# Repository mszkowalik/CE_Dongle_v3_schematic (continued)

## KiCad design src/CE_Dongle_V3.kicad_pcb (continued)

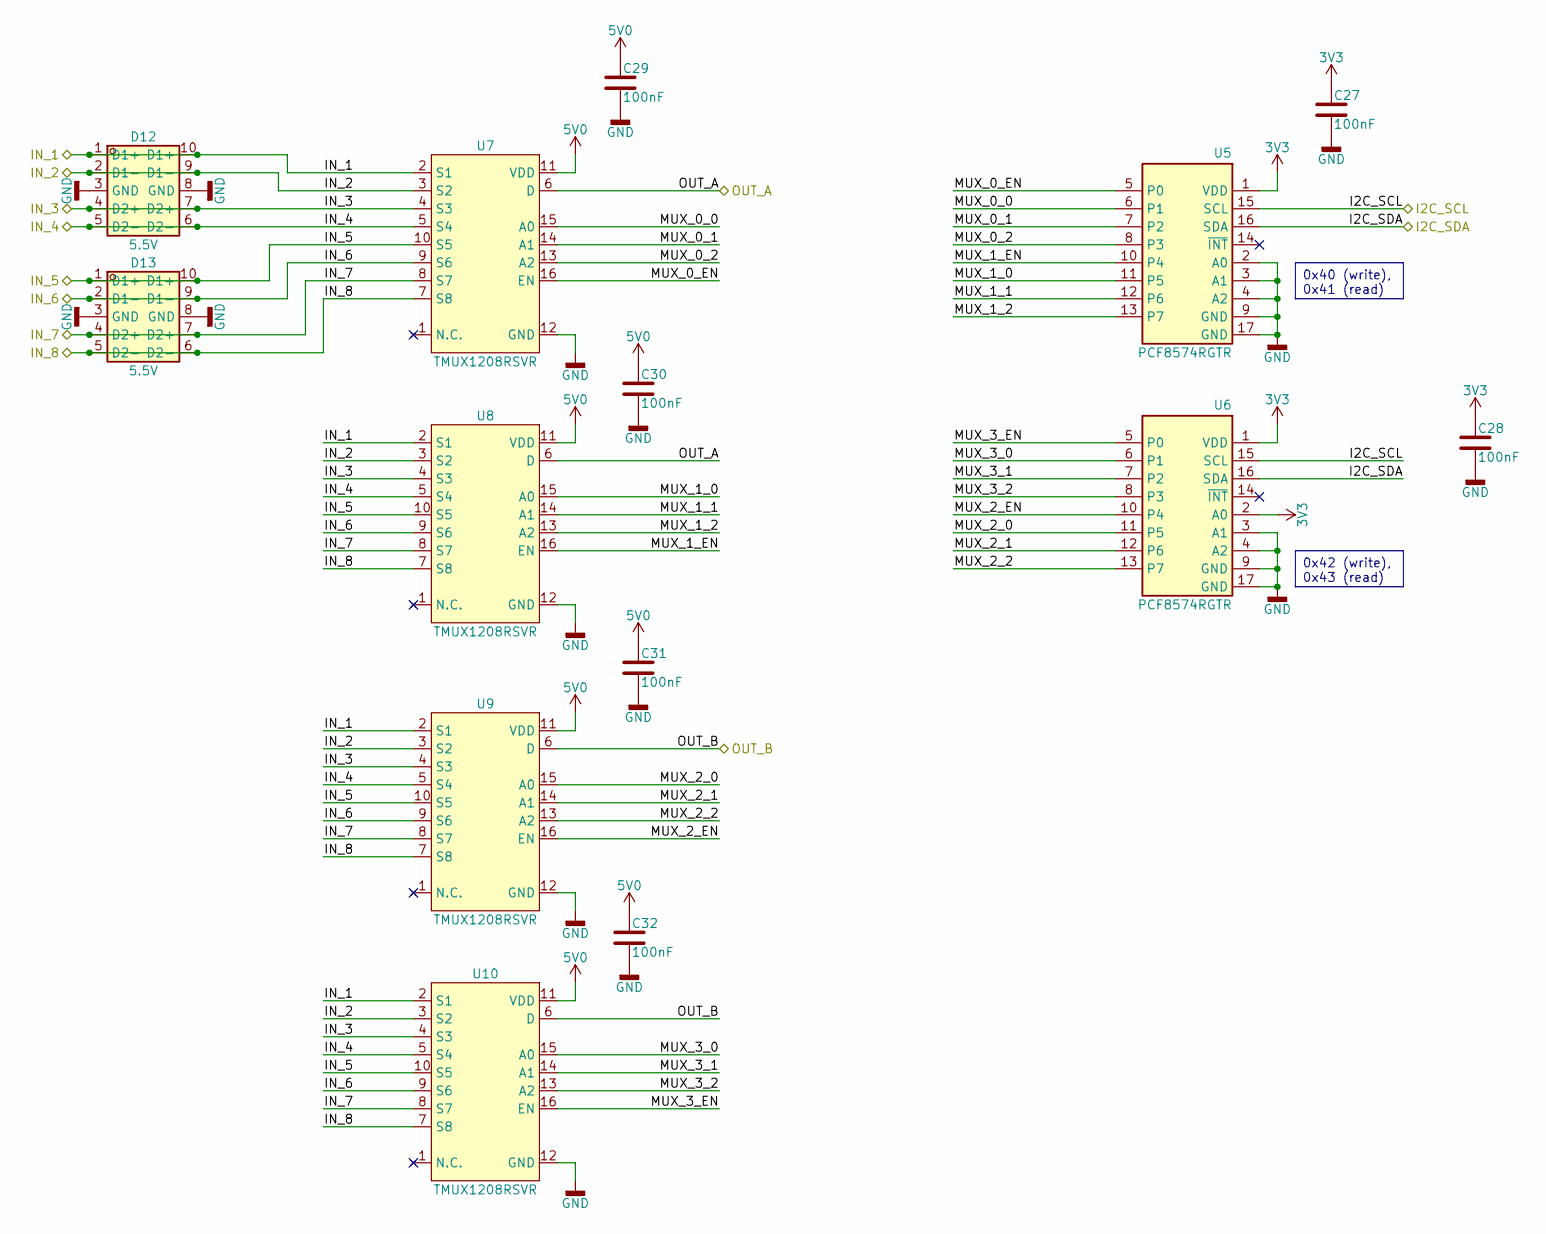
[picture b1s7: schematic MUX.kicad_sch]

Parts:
C27, C28, C29, C30, C31, C32: 100nF; C_0402_1005Metric; Voltage 16V; Tolerance 10%; Manufacturer Part Numbe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 CL05B104KO5NNNC; LCSC Part C1525
D12, D13: 5.5V; USON-10_2.5x1.0mm_P0.5mm; Voltage - Breakdown 6.5V; LCSC Part C138714
U5, U6: PCF8574RGTR; QFN-16-1EP_3x3mm_P0.5mm_EP1.7x1.7mm_ThermalVias; Manufacturer Part Numbe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 PCF8574RGTR; LCSC Part C22396384
U7, U8, U9, U10: TMUX1208RSVR; UQFN-16_1.8x2.6mm_P0.4mm; Manufacturer Part Numbe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 TMUX1208RSVR; LCSC Part C2673274

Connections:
3V3: C27.1, C28.1, U5.1 (VDD), U6.1 (VDD), U6.2 (A0); also elsewhere on the board
5V0: C29.1, C30.1, C31.1, C32.1, U7.11 (VDD), U8.11 (VDD), U9.11 (VDD), U10.11 (VDD); also elsewhere on the board
/MCU/I2C_SCL: U5.15 (SCL), U6.15 (SCL); also elsewhere on the board
/MCU/I2C_SDA: U5.16 (SDA), U6.16 (SDA); also elsewhere on the board
/MUX/IN_1: D12.1 (D1+), D12.10 (D1+), U7.2 (S1), U8.2 (S1), U9.2 (S1), U10.2 (S1); also elsewhere on the board
/MUX/IN_2: D12.2 (D1-), D12.9 (D1-), U7.3 (S2), U8.3 (S2), U9.3 (S2), U10.3 (S2); also elsewhere on the board
/MUX/IN_3: D12.4 (D2+), D12.7 (D2+), U7.4 (S3), U8.4 (S3), U9.4 (S3), U10.4 (S3); also elsewhere on the board
/MUX/IN_4: D12.5 (D2-), D12.6 (D2-), U7.5 (S4), U8.5 (S4), U9.5 (S4), U10.5 (S4); also elsewhere on the board
/MUX/IN_5: D13.1 (D1+), D13.10 (D1+), U7.10 (S5), U8.10 (S5), U9.10 (S5), U10.10 (S5); also elsewhere on the board
/MUX/IN_6: D13.2 (D1-), D13.9 (D1-), U7.9 (S6), U8.9 (S6), U9.9 (S6), U10.9 (S6); also elsewhere on the board
/MUX/IN_7: D13.4 (D2+), D13.7 (D2+), U7.8 (S7), U8.8 (S7), U9.8 (S7), U10.8 (S7); also elsewhere on the board
/MUX/IN_8: D13.5 (D2-), D13.6 (D2-), U7.7 (S8), U8.7 (S8), U9.7 (S8), U10.7 (S8); also elsewhere on the board
/MUX/MUX_0_0: U5.6 (P1), U7.15 (A0)
/MUX/MUX_0_1: U5.7 (P2), U7.14 (A1)
/MUX/MUX_0_2: U5.8 (P3), U7.13 (A2)
/MUX/MUX_0_EN: U5.5 (P0), U7.16 (EN)
/MUX/MUX_1_0: U5.11 (P5), U8.15 (A0)
/MUX/MUX_1_1: U5.12 (P6), U8.14 (A1)
/MUX/MUX_1_2: U5.13 (P7), U8.13 (A2)
/MUX/MUX_1_EN: U5.10 (P4), U8.16 (EN)
/MUX/MUX_2_0: U6.11 (P5), U9.15 (A0)
/MUX/MUX_2_1: U6.12 (P6), U9.14 (A1)
/MUX/MUX_2_2: U6.13 (P7), U9.13 (A2)
/MUX/MUX_2_EN: U6.10 (P4), U9.16 (EN)
/MUX/MUX_3_0: U6.6 (P1), U10.15 (A0)
/MUX/MUX_3_1: U6.7 (P2), U10.14 (A1)
/MUX/MUX_3_2: U6.8 (P3), U10.13 (A2)
/MUX/MUX_3_EN: U6.5 (P0), U10.16 (EN)
/MUX/OUT_A: U7.6 (D), U8.6 (D); also elsewhere on the board
/MUX/OUT_B: U9.6 (D), U10.6 (D); also elsewhere on the board
GND: C27.2, C28.2, C29.2, C30.2, C31.2, C32.2, D12.3 (GND), D12.8 (GND), D13.3 (GND), D13.8 (GND), U5.2 (A0), U5.3 (A1), U5.4 (A2), U5.9 (GND), U5.17 (GND), U6.3 (A1), U6.4 (A2), U6.9 (GND), U6.17 (GND), U7.12 (GND), U8.12 (GND), U9.12 (GND), U10.12 (GND); also elsewhere on the board

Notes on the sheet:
0x40 (write), 0x41 (read)
0x42 (write), 0x43 (read)

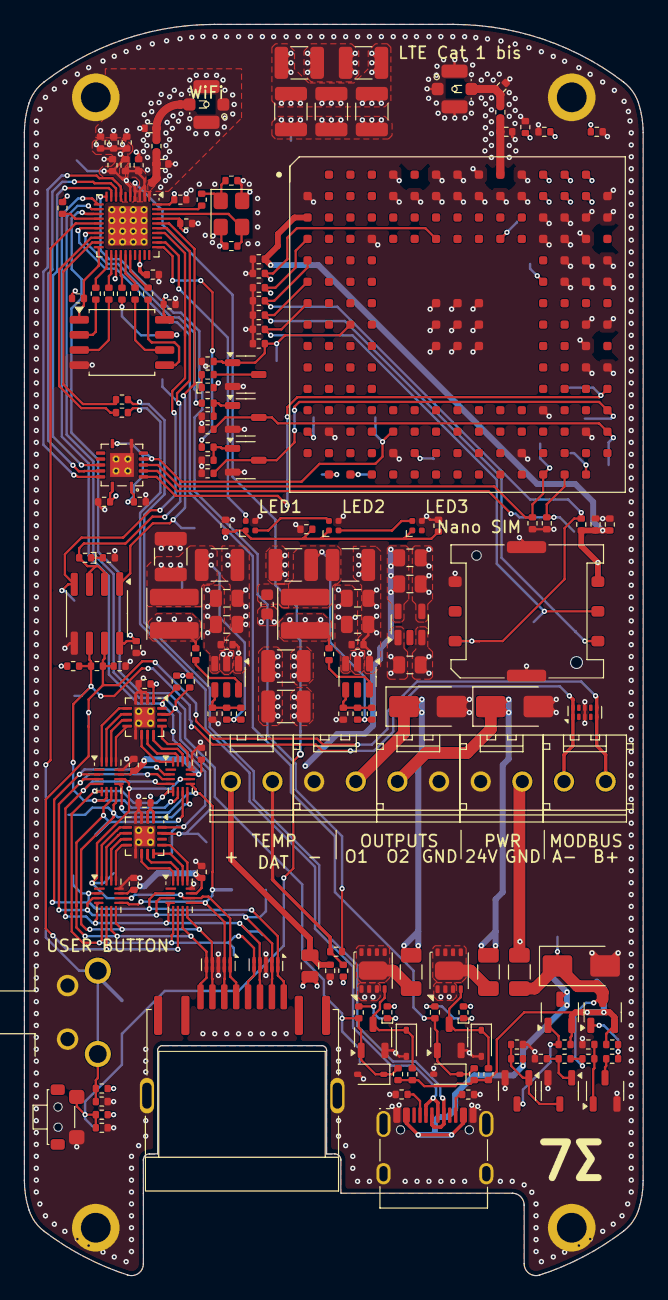
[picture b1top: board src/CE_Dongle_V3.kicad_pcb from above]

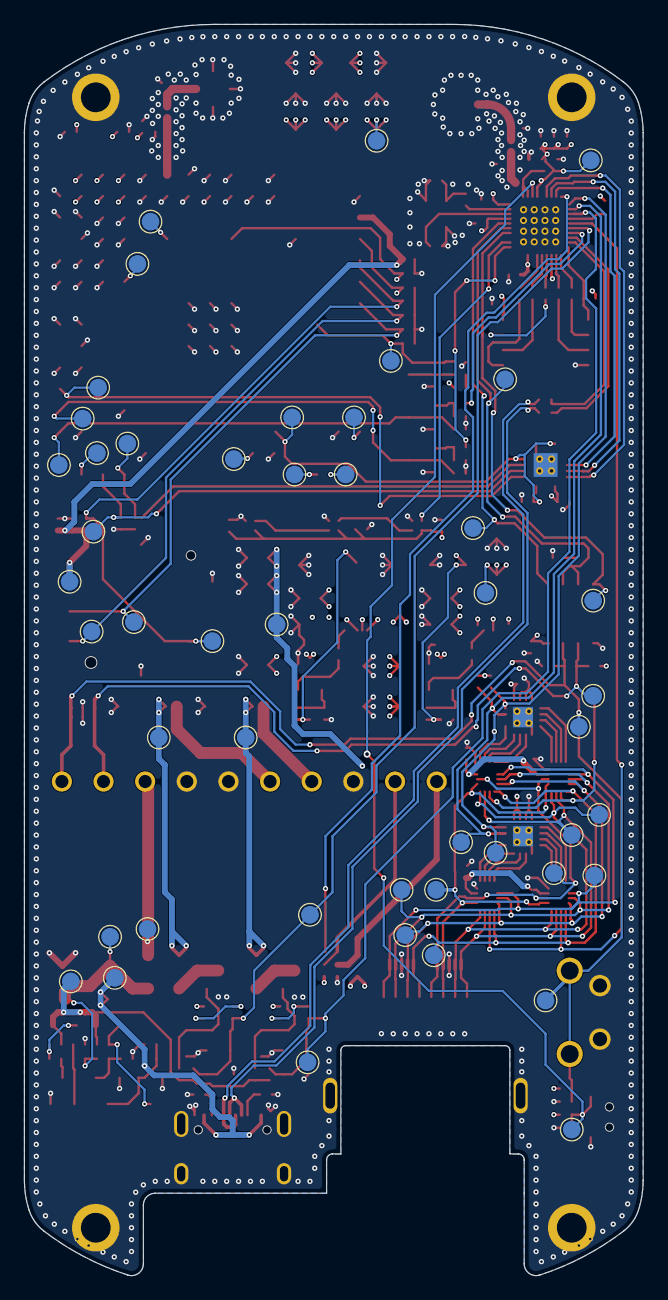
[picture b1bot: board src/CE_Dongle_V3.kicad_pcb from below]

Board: 4 copper layers, 52.0 x 105.2 mm, 240 parts (47 on the bottom side), 127 nets.

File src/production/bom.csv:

Designator,Footprint,Quantity,Value,LCSC Part #
"C1, C24, C4, C64",0402,4,1uF,C1518208
"C10, C11, C19, C22, C25, C26, C27, C28, C29, C30, C31, C32, C40, C46, C47, C48, C49, C50, C51, C54, C6, C66, C7, C8, C81, C9, C90, C91, C92",0402,29,100nF,C1525
"C12, C13",0402,2,10uF,C315248
"C14, C15",0402,2,1.2pF,C76899
"C16, C17",0402,2,12pF,C106201
"C18, C20, C33, C34, C35, C36, C37, C38, C39, C82",0402,10,100pF,C1546
"C2, C21, C23, C80, C84, C85, C86, C87",0805,8,10uF,C440198
"C3, C42, C43, C44, C45, C5, C55, C56, C57, C78, C79, C83, C93",1210,13,47uF,C2932477
C41,0402,1,220pF,C107001
"C52, C53",0402,2,10nF,C15195
"C62, C63, C65, C67, C68, C69",0402,6,33pF,C107005
"D1, D10",D_SMA,2,SMAJ28CA,C148228
"D11, D6, D9",D_SMA,3,SS34,C727060
D12,D_SOD-123,1,5V1,C173407
"D2, D3, D5, D8",0402,4,LTST-C281KRKT,C364556
ENC1,HAMMOND_1551XFLGY,1,Hammond_1551XFLGY,
FB1,0603,1,68nH,C76893
J1,USB-3.1-SMD_U262-161N-4BVC11,1,USB_C_Receptacle_USB2.0_16P,C319148
"J10, J2, J3, J6, J8",CONN-TH_DB301V-3.5-2P-GN,5,Conn_01x02,C695629
"J4, J5",SMA-SMD_BWSMA-KE-P001,2,Conn_Coaxial,C496550
J7,RJ45-TH_RC01812,1,8P8C_LED_Shielded,C708645
J9,SIM-SMD_NANO-SIM-TL6P-H1.35,1,SIM_NANO_Socket,C7529385
"K1, K2",RELAY-SMD_G6K-2F-X-XX,2,G6K-2F-Y-TR DC5,C47190
"L1, L2",0402,2,2.2nH,C91240
"L4, L5, L6",L_Changjiang_FTC404030S,3,4.7uH,C39676083
"LP1, LP2, LP3",FIX-LEMB2-4.8V0-F,3,FIX-LEMB2-4.8V0-F,
"Q1, Q2",SOT-23-3,2,AO3401A,C15127
"Q11, Q12, Q13, Q14, Q15, Q16, Q17, Q18",SOT-23-3,8,SI2308A,C347491
"Q7, Q8",SOT-23-3,2,BC817-40-7-F,C435867
"R10, R11, R12, R13, R15, R16, R17",0402,7,22R,C25092
"R18, R44",0402,2,120R,C25079
"R2, R30, R48, R55, R56, R59, R6, R71",0402,8,22K,C25768
"R20, R29, R3, R4, R5, R57, R60",0402,7,1K,C11702
"R21, R22, R31, R35, R36, R45, R51, R52, R61, R69",0402,10,10K,C25744
"R25, R26, R27, R28, R33, R34, R39, R47, R62, R70, R72",0402,11,100K,C25741
"R37, R38, R40",0402,3,374K,C25781
"R42, R43, R49, R8, R9",0402,5,5K1,C25905
R46,0402,1,0R,C17168
R50,0805,1,120R,C17437
R58,0402,1,162K,C54068
R7,0402,1,118K,C25748
SW1,SW-SMD_TS24CA,1,TS24CA,C393942
SW2,SW-SMD_4P-L6.0-W6.0-P4.50-LS9.0-H7.0,1,KH-6X6X7H-STM,C2837533
"TP1, TP10, TP11, TP12, TP13, TP14, TP15, TP16, TP17, TP18, TP19, TP2, TP20, TP21, TP22, TP23, TP24, TP7, TP8, TP9",TestPoint_Pad_D1.5mm,20,TestPoint,
U1,VQFN-40-1EP_5x5mm_P0.4mm_EP3.3x3.3mm_ThermalVias,1,ESP32-C6,C5364646
"U10, U7, U8, U9",UQFN-16_1.8x2.6mm_P0.4mm,4,TMUX1208RSVR,C2673274
"U14, U19, U4",SOT-23-6,3,TPS54302DDCR,C311983
U15,VQFN-14_L3.5-W3.5-P0.50-BL-EP-ThermalVias,1,TXS0104ERGYR,C154926
U16,XCVR_LE910R1-EU,1,LE910R1,
"U17, U18, U20",LED-SMD_4P-L1.3-W1.3-P0.80_WS2812E-1313,3,WS2812,C5446700
U2,SOIC-8_3.9x4.9mm_P1.27mm,1,SP3485,C8963
U3,SOIC-8_5.3x5.3mm_P1.27mm,1,W25Q64JVSSIQ,C179171
"U5, U6",QFN-16-1EP_3x3mm_P0.5mm_EP1.7x1.7mm_ThermalVias,2,PCF8574RGTR(UMW),C22396384
Y1,Crystal_SMD_3225-4Pin_3.2x2.5mm,1,40MHz,C37635390

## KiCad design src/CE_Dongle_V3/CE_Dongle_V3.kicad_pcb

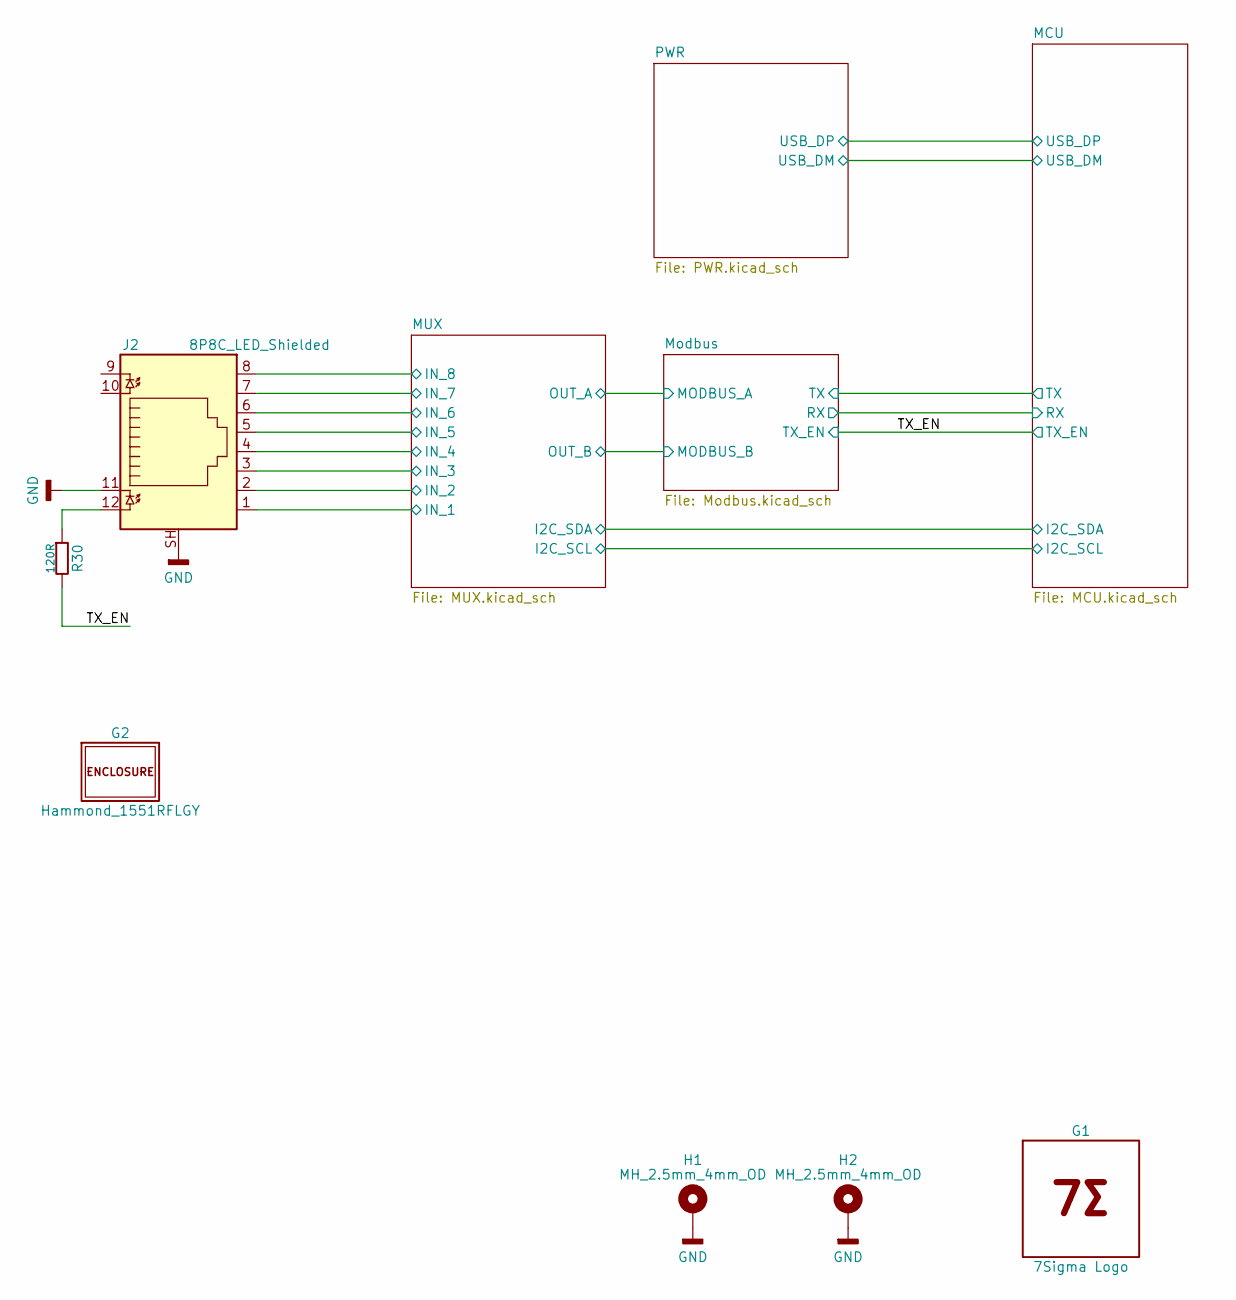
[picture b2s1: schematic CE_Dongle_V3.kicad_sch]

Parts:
G1: 7Sigma Logo; 7Sigma_Logo
G2: Hammond_1551RFLGY; HAMMOND_1551RFLGY
H1, H2: MH_2.5mm_4mm_OD; MountingHole_2.5mm_Pad_4mm
J2: 8P8C_LED_Shielded; RJ45-TH_RC01812; Manufacturer Part Numbe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 RC01812; LCSC Part C708645
R30: 120R; R_0402_1005Metric; Tolerance 1%; Manufacturer Part Numbe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 0402WGF1200TCE; LCSC Part C25079

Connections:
/MUX/MUX_IN_1: J2.1; also elsewhere on the board
/MUX/MUX_IN_2: J2.2; also elsewhere on the board
/MUX/MUX_IN_3: J2.3; also elsewhere on the board
/MUX/MUX_IN_4: J2.4; also elsewhere on the board
/MUX/MUX_IN_5: J2.5; also elsewhere on the board
/MUX/MUX_IN_6: J2.6; also elsewhere on the board
/MUX/MUX_IN_7: J2.7; also elsewhere on the board
/MUX/MUX_IN_8: J2.8; also elsewhere on the board
/TX_EN: R30.2; also elsewhere on the board
GND: H1.1, H2.1, J2.11, J2.SH; also elsewhere on the board
unnamed: J2.12, R30.1

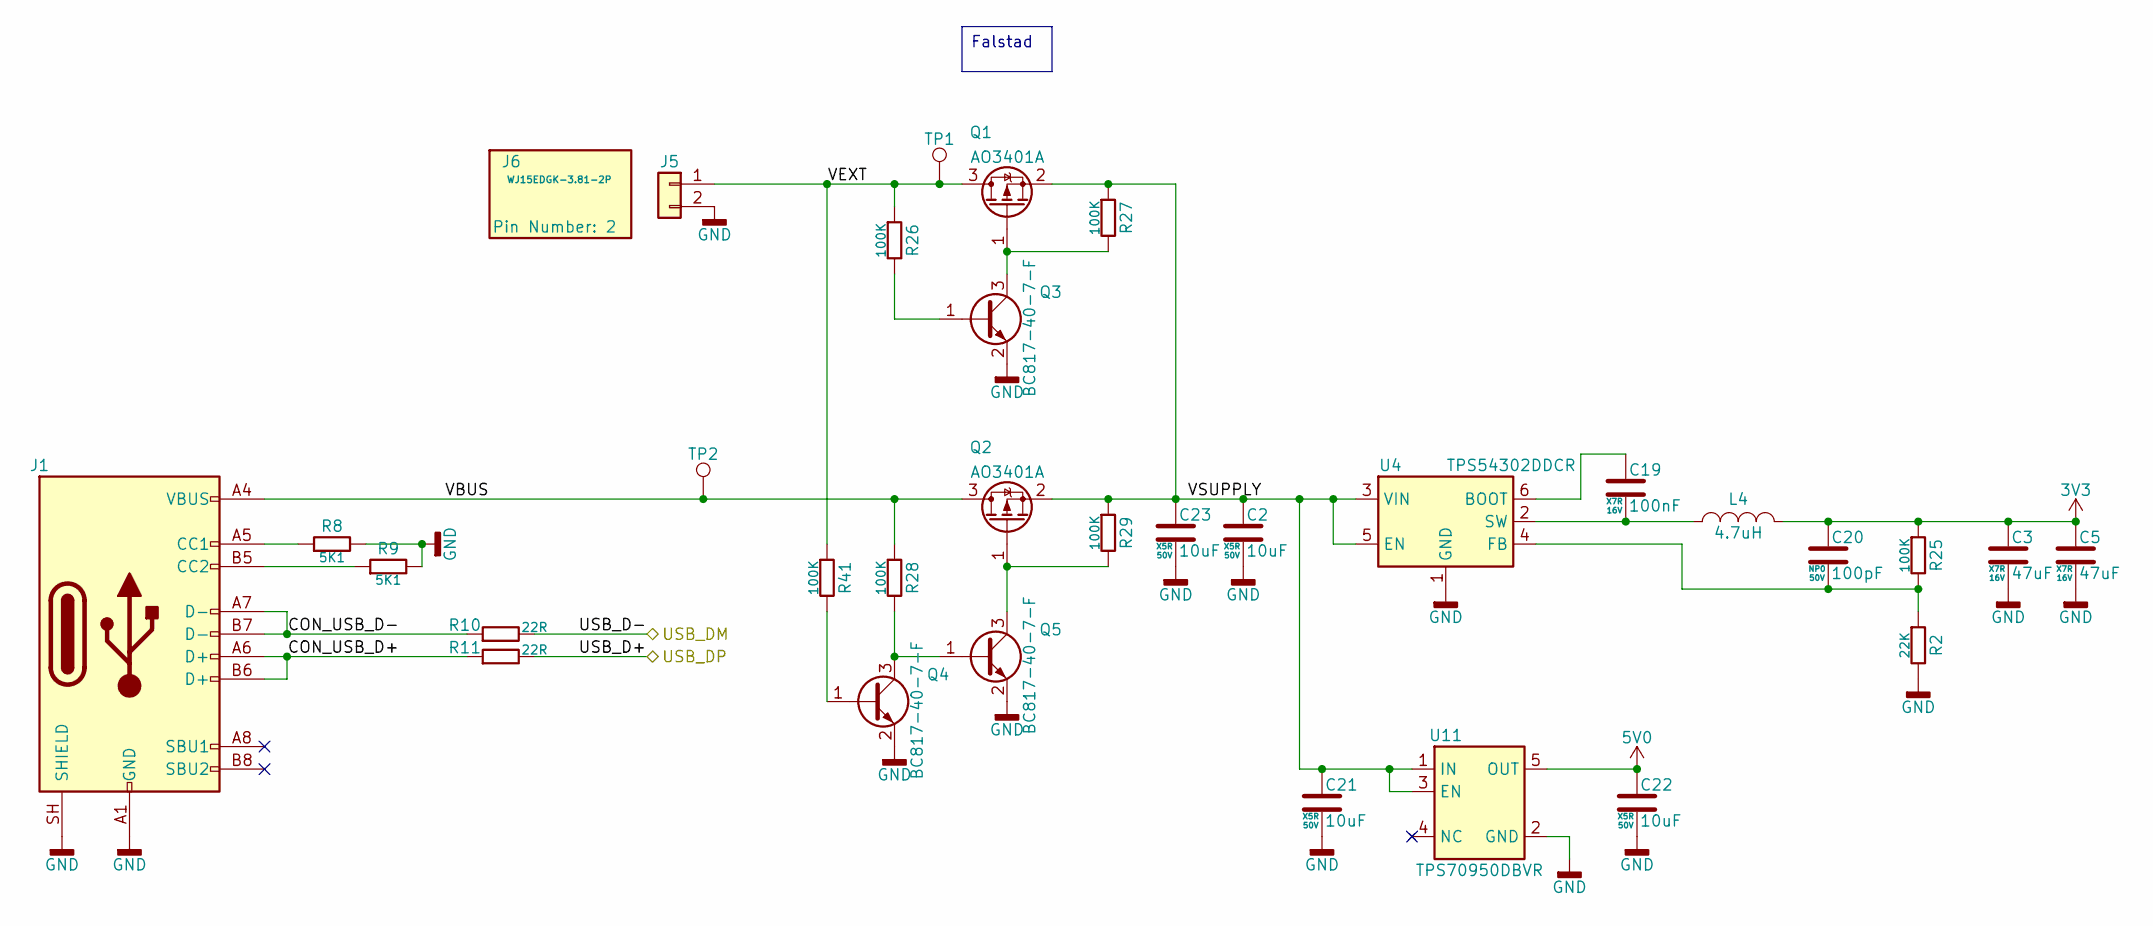
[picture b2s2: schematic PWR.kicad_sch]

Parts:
C2, C21, C22, C23: 10uF; C_0805_2012Metric; Voltage 50V; Tolerance 10%; Manufacturer Part Numbe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 GRM21BR61H106KE43L; LCSC Part C440198
C3, C5: 47uF; C_1210_3225Metric; Voltage 16V; Tolerance 10%; Manufacturer Part Numbe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 CS3225X7R476K160NRL; LCSC Part C5440143
C19: 100nF; C_0402_1005Metric; Voltage 16V; Tolerance 10%; Manufacturer Part Numbe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 CL05B104KO5NNNC; LCSC Part C1525
C20: 100pF; C_0402_1005Metric; Voltage 50V; Tolerance 5%; Manufacturer Part Numbe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 CC0402JRNPO9BN101; LCSC Part C106200
J1: USB_C_Receptacle_USB2.0_16P; USB-3.1-SMD_U262-161N-4BVC11; Manufacturer Part Numbe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 U262-161N-4BVC11; LCSC Part C319148
J5: Conn_01x02; PhoenixContact_MC_1,5_2-G-3.81_1x02_P3.81mm_Horizontal; Manufacturer Part Numbe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 WJ15EDGRC-3.81-2P; LCSC Part C8387
J6: WJ15EDGK-3.81-2P; TerminalBlock_Plug_Invisible; Manufacturer Part Numbe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 WJ15EDGK-3.81-2P; LCSC Part C8466
L4: 4.7uH; L_Changjiang_FTC404030S; Tolerance 20%; Manufacturer Part Numbe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 FTC404030S4R7MGCA; LCSC Part C39676083
Q1, Q2: AO3401A; SOT-23; Manufacturer Part Numbe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 AO3401A; LCSC Part C15127
Q3, Q4, Q5: BC817-40-7-F; SOT-23; Manufacturer Part Numbe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 BC817-40-7-F; LCSC Part C435867
R2: 22K; R_0402_1005Metric; Tolerance 1%; Manufacturer Part Numbe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 0402WGF2202TCE; LCSC Part C25768
R8, R9: 5K1; R_0402_1005Metric; Tolerance 1%; Manufacturer Part Numbe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 0402WGF5101TCE; LCSC Part C25905
R10, R11: 22R; R_0402_1005Metric; Tolerance 1%; Manufacturer Part Numbe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 0402WGF220JTCE; LCSC Part C25092
R25, R26, R27, R28, R29, R41: 100K; R_0402_1005Metric; Tolerance 1%; Manufacturer Part Numbe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 0402WGF1003TCE; LCSC Part C25741
TP1, TP2: TestPoint; TestPoint_Pad_D1.5mm
U4: TPS54302DDCR; SOT-23-6; Manufacturer Part Numbe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 TPS54302DDCR; LCSC Part C311983
U11: TPS70950DBVR; SOT-23-5; Manufacturer Part Numbe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 TPS70950DBVR; LCSC Part C96028

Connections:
5V0: C22.1, U11.5 (OUT); also elsewhere on the board
/MCU/USB_D+: R11.2; also elsewhere on the board
/MCU/USB_D-: R10.2; also elsewhere on the board
/PWR/CON_USB_D+: J1.A6 (D+), J1.B6 (D+), R11.1
/PWR/CON_USB_D-: J1.A7 (D-), J1.B7 (D-), R10.1
/PWR/VBUS: J1.A4 (VBUS), J1.A9 (VBUS), J1.B4 (VBUS), J1.B9 (VBUS), Q2.3 (D), R28.1, TP2.1
/PWR/VEXT: J5.1, Q1.3 (D), R26.1, R41.1, TP1.1
/PWR/VSUPPLY: C2.1, C21.1, C23.1, Q1.2 (S), Q2.2 (S), R27.1, R29.1, U4.3 (VIN), U4.5 (EN), U11.1 (IN), U11.3 (EN)
GND: C2.2, C3.2, C5.2, C21.2, C22.2, C23.2, J1.A1 (GND), J1.A12 (GND), J1.B1 (GND), J1.B12 (GND), J1.SH (SHIELD), J5.2, Q3.2 (E), Q4.2 (E), Q5.2 (E), R2.2, R8.2, R9.2, U4.1 (GND), U11.2 (GND); also elsewhere on the board
unnamed: J1.A5 (CC1), R8.1
unnamed: J1.B5 (CC2), R9.1
unnamed: Q1.1 (G), Q3.3 (C), R27.2
unnamed: Q2.1 (G), Q5.3 (C), R29.2
unnamed: Q3.1 (B), R26.2
unnamed: Q4.1 (B), R41.2
unnamed: Q4.3 (C), Q5.1 (B), R28.2
unnamed: C19.1, U4.6 (BOOT)
unnamed: C20.2, R2.1, R25.2, U4.4 (FB)
unnamed: C19.2, L4.1, U4.2 (SW)

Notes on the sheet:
Falstad

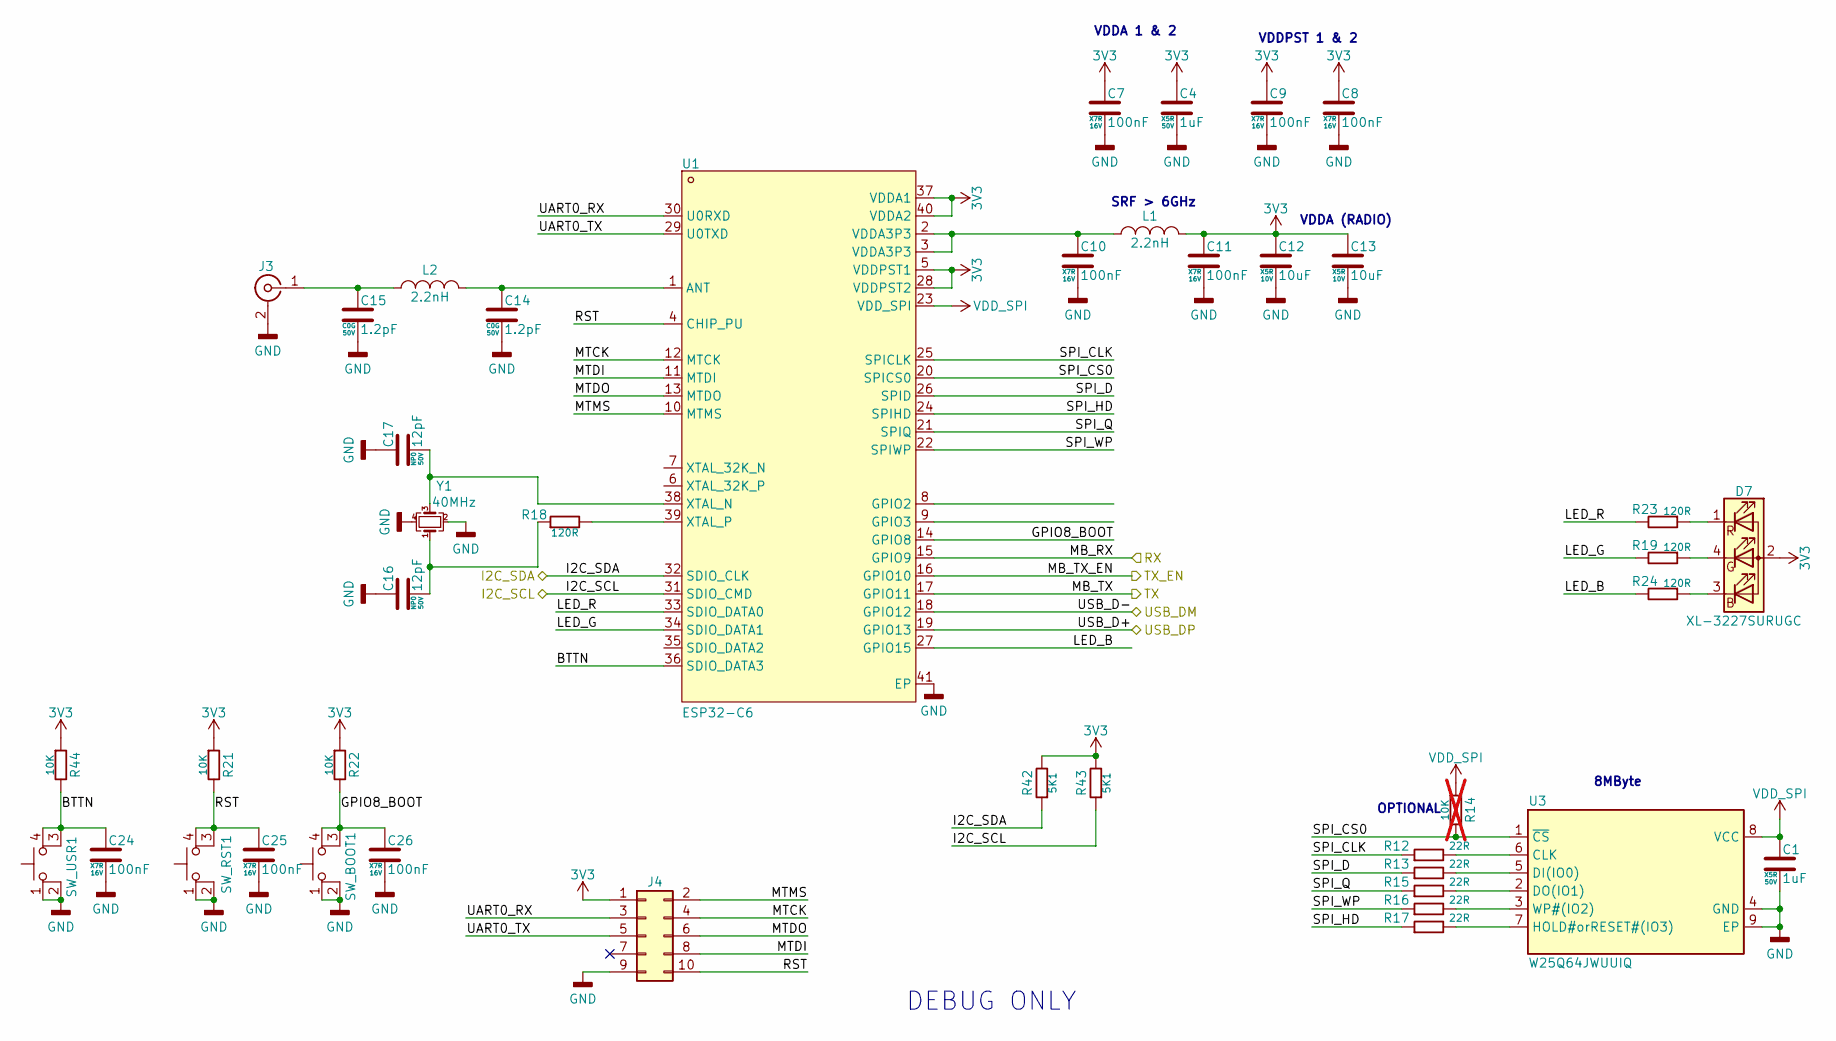
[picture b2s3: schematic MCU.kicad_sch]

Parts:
C1, C4: 1uF; C_0402_1005Metric; Voltage 50V; Tolerance 1%; Manufacturer Part Numbe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 GRM155R61H105KE05D; LCSC Part C1518208
C7, C8, C9, C10, C11, C24, C25, C26: 100nF; C_0402_1005Metric; Voltage 16V; Tolerance 10%; Manufacturer Part Numbe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 CL05B104KO5NNNC; LCSC Part C1525
C12, C13: 10uF; C_0402_1005Metric; Voltage 10V; Tolerance 10%; Manufacturer Part Numbe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 CL05A106MP5NUNC; LCSC Part C315248
C14, C15: 1.2pF; C_0402_1005Metric; Voltage 50V; Tolerance 0.05pF; Manufacturer Part Numbe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 GJM1555C1H1R2WB01D; LCSC Part C76899
C16, C17: 12pF; C_0402_1005Metric; Voltage 50V; Tolerance 5%; Manufacturer Part Numbe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 CC0402JRNPO9BN120; LCSC Part C106201
D7: XL-3227SURUGC; LED-SMD_4P-L1.6-W1.5-BR; Manufacturer Part Numbe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 XL-1615RGBC-RF; LCSC Part C965840
J3: Conn_Coaxial; SMA-SMD_BWSMA-KE-P001; Manufacturer Part Numbe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 BWSMA-KE-P001; LCSC Part C496550
J4: Conn_02x05_Odd_Even; IDC-SMD_10P-P1.27-3220-10-0300-00; Manufacturer Part Numbe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 HX JN1.27-2x5 TP H4.9; LCSC Part C42372555
L1, L2: 2.2nH; L_0402_1005Metric; Tolerance 10%; Manufacturer Part Numbe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 LQW15AN2N2C10D; LCSC Part C91240
R12, R13, R15, R16, R17: 22R; R_0402_1005Metric; Tolerance 1%; Manufacturer Part Numbe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 0402WGF220JTCE; LCSC Part C25092
R14: 10K; R_0402_1005Metric; Tolerance 1%; Manufacturer Part Numbe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 0402WGF1002TCE; LCSC Part C25744; not fitted
R18, R19, R23, R24: 120R; R_0402_1005Metric; Tolerance 1%; Manufacturer Part Numbe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 0402WGF1200TCE; LCSC Part C25079
R21, R22, R44: 10K; R_0402_1005Metric; Tolerance 1%; Manufacturer Part Numbe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 0402WGF1002TCE; LCSC Part C25744
R42, R43: 5K1; R_0402_1005Metric; Tolerance 1%; Manufacturer Part Numbe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 0402WGF5101TCE; LCSC Part C25905
SW_BOOT1: KH-6X6X4.3H-STM; SW-SMD_4P-L6.0-W6.0-P4.50-LS9.0-H4.3; Manufacturer Part Numbe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 KH-6X6X4.3H-STM; LCSC Part C2837530
SW_RST1: KH-6X6X4.3H-STM; SW-SMD_4P-L6.0-W6.0-P4.50-LS9.0-H4.3; Manufacturer Part Numbe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 KH-6X6X4.3H-STM; LCSC Part C2837530
SW_USR1: KH-6X6X4.3H-STM; SW-SMD_4P-L6.0-W6.0-P4.50-LS9.0-H4.3; Manufacturer Part Numbe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 KH-6X6X4.3H-STM; LCSC Part C2837530
U1: ESP32-C6; VQFN-40-1EP_5x5mm_P0.4mm_EP3.3x3.3mm_ThermalVias; Manufacturer Part Numbe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 ESP32-C6; LCSC Part C5364646
U3: W25Q64JWUUIQ; Winbond_USON-8-2EP_3x4mm_P0.8mm_EP0.2x0.8mm; Manufacturer Part Numbe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 W25Q64JWUUIQ; LCSC Part C6604692
Y1: 40MHz; Crystal_SMD_3225-4Pin_3.2x2.5mm; Tolerance 10ppm; Manufacturer Part Numbe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 XTM32040000FT00351001; LCSC Part C37635390

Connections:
/MCU/BTTN: C24.1, R44.2, SW_USR1.3 (K), SW_USR1.4 (A), U1.36 (SDIO_DATA3)
/MCU/GPIO8_BOOT: C26.1, R22.2, SW_BOOT1.3 (K), SW_BOOT1.4 (A), U1.14 (GPIO8)
/MCU/I2C_SCL: R43.1, U1.31 (SDIO_CMD); also elsewhere on the board
/MCU/I2C_SDA: R42.1, U1.32 (SDIO_CLK); also elsewhere on the board
/MCU/LED_B: R24.2, U1.27 (GPIO15)
/MCU/LED_G: R19.2, U1.34 (SDIO_DATA1)
/MCU/LED_R: R23.2, U1.33 (SDIO_DATA0)
/MCU/MB_RX: U1.15 (GPIO9); also elsewhere on the board
/MCU/MB_TX: U1.17 (GPIO11); also elsewhere on the board
/MCU/MTCK: J4.4, U1.12 (MTCK)
/MCU/MTDI: J4.8, U1.11 (MTDI)
/MCU/MTDO: J4.6, U1.13 (MTDO)
/MCU/MTMS: J4.2, U1.10 (MTMS)
/MCU/RST: C25.1, J4.10, R21.2, SW_RST1.3 (K), SW_RST1.4 (A), U1.4 (CHIP_PU)
/MCU/SPI_CLK: R12.1, U1.25 (SPICLK)
/MCU/SPI_CS0: R14.2, U1.20 (SPICS0), U3.1 (~CS)
/MCU/SPI_D: R13.1, U1.26 (SPID)
/MCU/SPI_HD: R17.1, U1.24 (SPIHD)
/MCU/SPI_Q: R15.1, U1.21 (SPIQ)
/MCU/SPI_WP: R16.1, U1.22 (SPIWP)
/MCU/UART0_RX: J4.3, U1.30 (U0RXD)
/MCU/UART0_TX: J4.5, U1.29 (U0TXD)
/MCU/USB_D+: U1.19 (GPIO13); also elsewhere on the board
/MCU/USB_D-: U1.18 (GPIO12); also elsewhere on the board
/TX_EN: U1.16 (GPIO10); also elsewhere on the board
GND: C1.2, C4.2, C7.2, C8.2, C9.2, C10.2, C11.2, C12.2, C13.2, C14.2, C15.2, C16.1, C17.1, C24.2, C25.2, C26.2, J3.2 (Ext), J4.9, SW_BOOT1.1, SW_BOOT1.2, SW_RST1.1, SW_RST1.2, SW_USR1.1, SW_USR1.2, U1.41 (EP), U3.4 (GND), U3.9 (EP), Y1.2, Y1.4; also elsewhere on the board
unnamed: C10.1, L1.1, U1.2 (VDDA3P3), U1.3 (VDDA3P3)
unnamed: C16.2, R18.1, Y1.1
unnamed: D7.3 (BK), R24.1
unnamed: D7.4 (GK), R19.1
unnamed: D7.1 (RK), R23.1
unnamed: C15.1, J3.1 (In), L2.1
unnamed: C14.1, L2.2, U1.1 (ANT)
unnamed: C17.2, U1.38 (XTAL_N), Y1.3
unnamed: R18.2, U1.39 (XTAL_P)
unnamed: R12.2, U3.6 (CLK)
unnamed: R13.2, U3.5 (DI(IO0))
unnamed: R15.2, U3.2 (DO(IO1))
unnamed: R17.2, U3.7 (HOLD#orRESET#(IO3))
unnamed: R16.2, U3.3 (WP#(IO2))
VDD_SPI: C1.1, R14.1, U1.23 (VDD_SPI), U3.8 (VCC)

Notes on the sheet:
DEBUG ONLY
VDDA (RADIO)
OPTIONAL
SRF > 6GHz
VDDA 1 & 2
8MByte
VDDPST 1 & 2

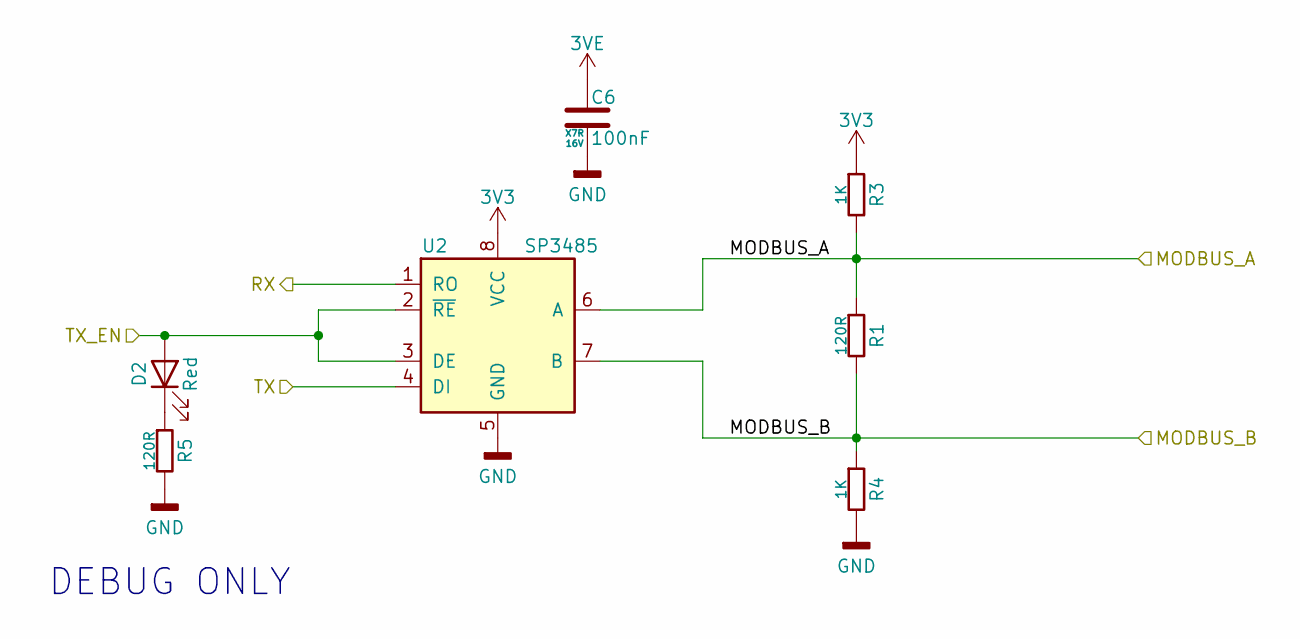
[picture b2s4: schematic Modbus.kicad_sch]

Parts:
C6: 100nF; C_0402_1005Metric; Voltage 16V; Tolerance 10%; Manufacturer Part Numbe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 CL05B104KO5NNNC; LCSC Part C1525
D2: LTST-C281KRKT; LED_0402_1005Metric; Forward Voltage 2V; Manufacturer Part Numbe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 LTST-C281KRKT; LCSC Part C364556
R1, R5: 120R; R_0402_1005Metric; Tolerance 1%; Manufacturer Part Numbe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 0402WGF1200TCE; LCSC Part C25079
R3, R4: 1K; R_0402_1005Metric; Tolerance 1%; Manufacturer Part Numbe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 0402WGF1001TCE; LCSC Part C11702
U2: SP3485; SOIC-8_3.9x4.9mm_P1.27mm; Manufacturer Part Numbe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 SP3485EN-L/TR; LCSC Part C8963

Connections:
/MCU/MB_RX: U2.1 (RO); also elsewhere on the board
/MCU/MB_TX: U2.4 (DI); also elsewhere on the board
/MUX/OUT_A: R1.1, R3.2, U2.6 (A); also elsewhere on the board
/MUX/OUT_B: R1.2, R4.1, U2.7 (B); also elsewhere on the board
/TX_EN: D2.2 (A), U2.2 (~RE), U2.3 (DE); also elsewhere on the board
GND: C6.2, R4.2, R5.2, U2.5 (GND); also elsewhere on the board
unnamed: D2.1 (K), R5.1

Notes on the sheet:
DEBUG ONLY

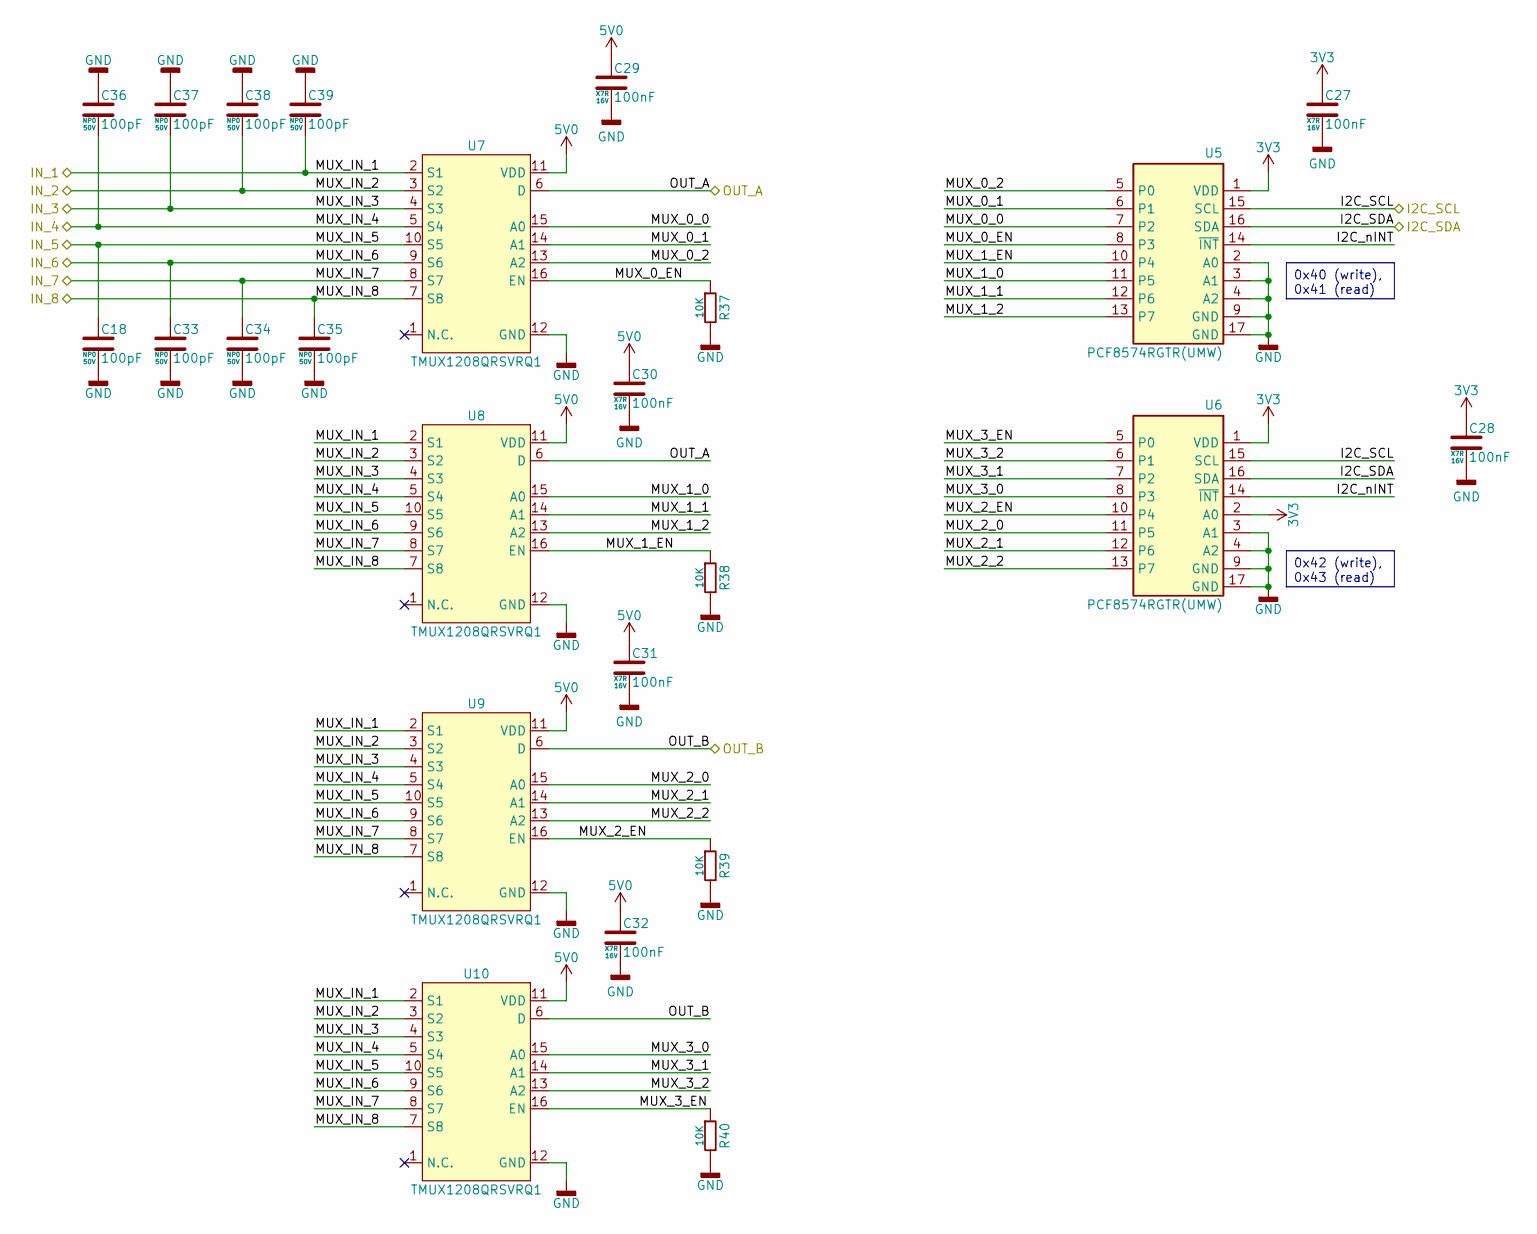
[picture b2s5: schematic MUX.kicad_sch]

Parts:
C18, C33, C34, C35, C36, C37, C38, C39: 100pF; C_0402_1005Metric; Voltage 50V; Tolerance 5%; Manufacturer Part Numbe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 CC0402JRNPO9BN101; LCSC Part C106200
C27, C28, C29, C30, C31, C32: 100nF; C_0402_1005Metric; Voltage 16V; Tolerance 10%; Manufacturer Part Numbe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 CL05B104KO5NNNC; LCSC Part C1525
R37, R38, R39, R40: 10K; R_0402_1005Metric; Tolerance 1%; Manufacturer Part Numbe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 0402WGF1002TCE; LCSC Part C25744
U5, U6: PCF8574RGTR(UMW); QFN-16-1EP_3x3mm_P0.5mm_EP1.7x1.7mm_ThermalVias; Manufacturer Part Numbe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 PCF8574RGTR(UMW); LCSC Part C22396384
U7, U8, U9, U10: TMUX1208QRSVRQ1; UQFN-16_1.8x2.6mm_P0.4mm; Manufacturer Part Numbe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 TMUX1208QRSVRQ1; LCSC Part C2876797

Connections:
5V0: C29.1, C30.1, C31.1, C32.1, U7.11 (VDD), U8.11 (VDD), U9.11 (VDD), U10.11 (VDD); also elsewhere on the board
/MCU/I2C_SCL: U5.15 (SCL), U6.15 (SCL); also elsewhere on the board
/MCU/I2C_SDA: U5.16 (SDA), U6.16 (SDA); also elsewhere on the board
/MUX/I2C_nINT: U5.14 (~INT), U6.14 (~INT)
/MUX/MUX_0_0: U5.7 (P2), U7.15 (A0)
/MUX/MUX_0_1: U5.6 (P1), U7.14 (A1)
/MUX/MUX_0_2: U5.5 (P0), U7.13 (A2)
/MUX/MUX_0_EN: R37.1, U5.8 (P3), U7.16 (EN)
/MUX/MUX_1_0: U5.11 (P5), U8.15 (A0)
/MUX/MUX_1_1: U5.12 (P6), U8.14 (A1)
/MUX/MUX_1_2: U5.13 (P7), U8.13 (A2)
/MUX/MUX_1_EN: R38.1, U5.10 (P4), U8.16 (EN)
/MUX/MUX_2_0: U6.11 (P5), U9.15 (A0)
/MUX/MUX_2_1: U6.12 (P6), U9.14 (A1)
/MUX/MUX_2_2: U6.13 (P7), U9.13 (A2)
/MUX/MUX_2_EN: R39.1, U6.10 (P4), U9.16 (EN)
/MUX/MUX_3_0: U6.8 (P3), U10.15 (A0)
/MUX/MUX_3_1: U6.7 (P2), U10.14 (A1)
/MUX/MUX_3_2: U6.6 (P1), U10.13 (A2)
/MUX/MUX_3_EN: R40.1, U6.5 (P0), U10.16 (EN)
/MUX/MUX_IN_1: C39.2, U7.2 (S1), U8.2 (S1), U9.2 (S1), U10.2 (S1); also elsewhere on the board
/MUX/MUX_IN_2: C38.2, U7.3 (S2), U8.3 (S2), U9.3 (S2), U10.3 (S2); also elsewhere on the board
/MUX/MUX_IN_3: C37.2, U7.4 (S3), U8.4 (S3), U9.4 (S3), U10.4 (S3); also elsewhere on the board
/MUX/MUX_IN_4: C36.2, U7.5 (S4), U8.5 (S4), U9.5 (S4), U10.5 (S4); also elsewhere on the board
/MUX/MUX_IN_5: C18.1, U7.10 (S5), U8.10 (S5), U9.10 (S5), U10.10 (S5); also elsewhere on the board
/MUX/MUX_IN_6: C33.1, U7.9 (S6), U8.9 (S6), U9.9 (S6), U10.9 (S6); also elsewhere on the board
/MUX/MUX_IN_7: C34.1, U7.8 (S7), U8.8 (S7), U9.8 (S7), U10.8 (S7); also elsewhere on the board
/MUX/MUX_IN_8: C35.1, U7.7 (S8), U8.7 (S8), U9.7 (S8), U10.7 (S8); also elsewhere on the board
/MUX/OUT_A: U7.6 (D), U8.6 (D); also elsewhere on the board
/MUX/OUT_B: U9.6 (D), U10.6 (D); also elsewhere on the board
GND: C18.2, C27.2, C28.2, C29.2, C30.2, C31.2, C32.2, C33.2, C34.2, C35.2, C36.1, C37.1, C38.1, C39.1, R37.2, R38.2, R39.2, R40.2, U5.2 (A0), U5.3 (A1), U5.4 (A2), U5.9 (GND), U5.17 (GND), U6.3 (A1), U6.4 (A2), U6.9 (GND), U6.17 (GND), U7.12 (GND), U8.12 (GND), U9.12 (GND), U10.12 (GND); also elsewhere on the board

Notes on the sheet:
0x40 (write), 0x41 (read)
0x42 (write), 0x43 (read)

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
